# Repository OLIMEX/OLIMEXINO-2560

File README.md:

# OLIMEXINO-2560
Arduino Mega 2560 like board with ATMEGA2560 processor, 88 GPIOs, uSD card, 6-15VDC power

## License
* Software Licensee is GPL 3.0
* Hardware Licensee is CERN Open Hardware Licence v1.2
* Documentation is released under CC BY-SA 3.0

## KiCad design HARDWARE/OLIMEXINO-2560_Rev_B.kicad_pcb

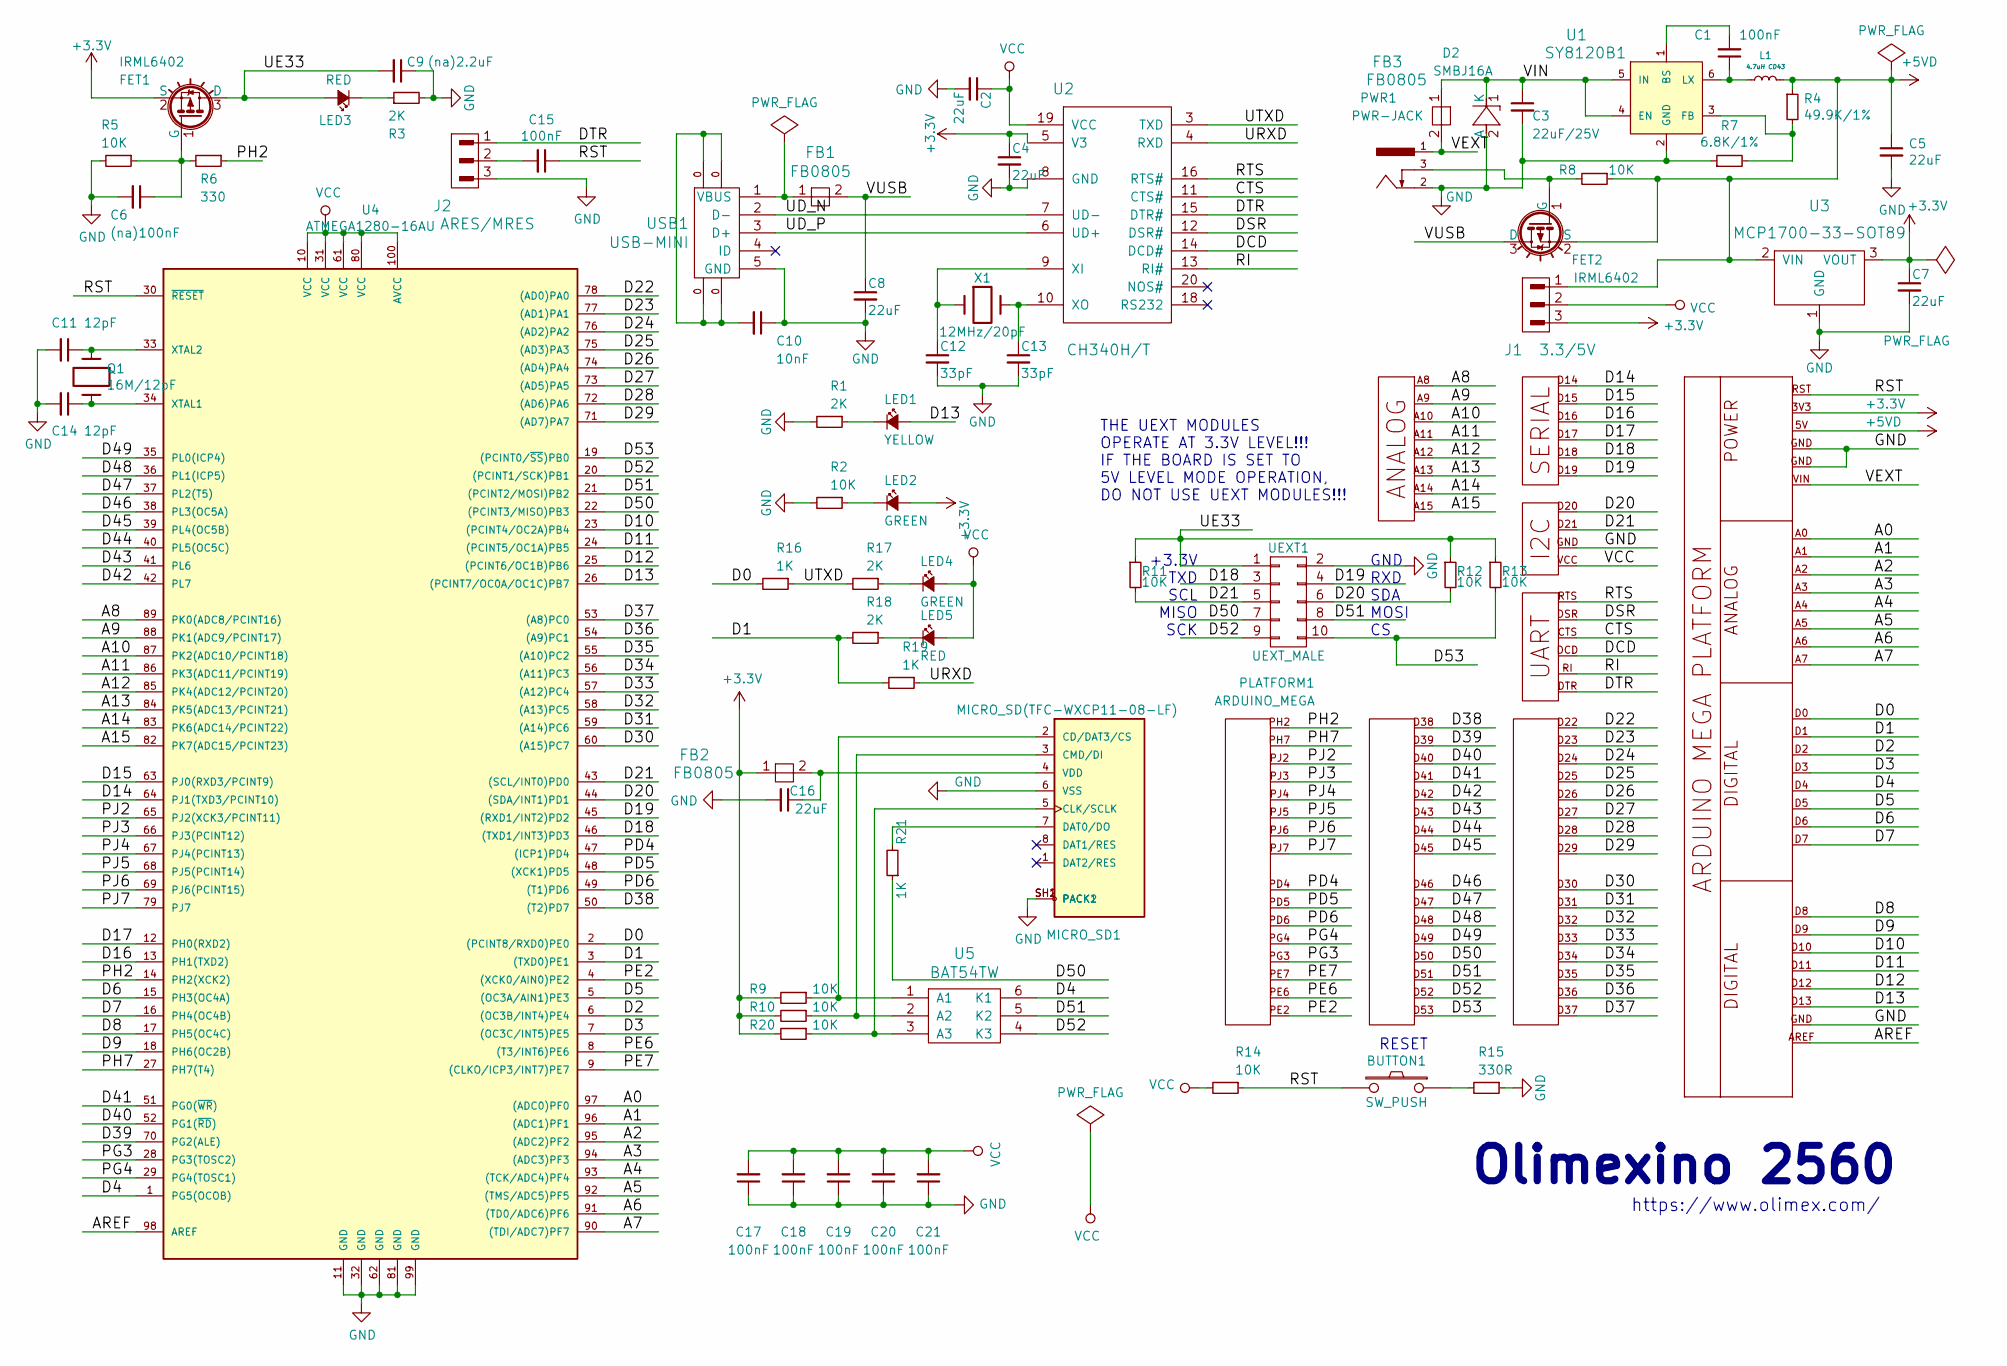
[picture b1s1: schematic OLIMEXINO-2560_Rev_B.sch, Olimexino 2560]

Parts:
BUTTON1: SW_PUSH; TSW34-W16PR-220
C1, C15, C17, C18, C19, C20, C21: 100nF; C_0402_5MIL_DWS
C2, C4, C5, C7, C8, C16: 22uF; C_0603_5MIL_DWS
C3: 22uF/25V; C_1206_5MIL_DWS
C6: (na)100nF; C_0402_5MIL_DWS
C9: (na)2.2uF; C_0603_5MIL_DWS
C10: 10nF; C_0603_5MIL_DWS
C11, C14: 12pF; C_0402_SMALL
C12, C13: 33pF; 0402
D2: SMBJ16A; SMB-KA
FB1, FB2, FB3: FB0805; L_0805_5MIL_DWS
FET1, FET2: IRML6402; SOT23
J1: 3.3/5V; HN1x3
J2: ARES/MRES; HN1x3
L1: 4.7uH CD43; CD43
LED1: YELLOW; LED_0603_KA_NOSILK
LED2, LED4: GREEN; LED_0603_KA_NOSILK
LED3, LED5: RED; LED_0603_KA_NOSILK
MICRO_SD1: MICRO_SD(TFC-WXCP11-08-LF); TFC-WXCP11-08-LF
PLATFORM1: ARDUINO_MEGA; OLIMEX_CASES-ARDUINO-MEGA-PLATFORM
PWR1: PWR-JACK; PWRJACK-FLAT
Q1: 16M/12pF; HCX-4S_2Pins_5.0x3.2mm
R1, R3, R17, R18: 2K; R_0402_5MIL_DWS
R2, R5, R8, R9, R10, R11, R12, R13, R14, R20: 10K; R_0402_5MIL_DWS
R4: 49.9K/1%; R_0603_5MIL_DWS
R6: 330; R_0402_5MIL_DWS
R7: 6.8K/1%; R_0402_5MIL_DWS
R15: 330R; R_0402_5MIL_DWS
R16, R19, R21: 1K; R_0402_5MIL_DWS
U1: SY8120B1; SOT23-6
U2: CH340H/T; SSOP-20W
U3: MCP1700-33-SOT89; SOT89
U4: ATMEGA1280-16AU; TQFP100
U5: BAT54TW; SOT363
UEXT1: UEXT_MALE; UEXT_BH10R
USB1: USB-MINI; MICRO_USB_5P-F_TYPE_DIP
X1: 12MHz/20pF; Q_49U3HMS

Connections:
+3V3: C4.1, C7.1, FB2.1, FET1.2 (S), J1.3, LED2.2 (A), PLATFORM1.3V3, R9.2, R10.2, R20.2, U2.5 (V3), U3.3 (VOUT)
+5VD: C5.1, FET2.2 (S), J1.1, L1.2, PLATFORM1.5V, R4.1, R8.1, U3.2 (VIN)
/A0: PLATFORM1.A0, U4.97 ((ADC0)PF0)
/A1: PLATFORM1.A1, U4.96 ((ADC1)PF1)
/A2: PLATFORM1.A2, U4.95 ((ADC2)PF2)
/A3: PLATFORM1.A3, U4.94 ((ADC3)PF3)
/A4: PLATFORM1.A4, U4.93 ((TCK/ADC4)PF4)
/A5: PLATFORM1.A5, U4.92 ((TMS/ADC5)PF5)
/A6: PLATFORM1.A6, U4.91 ((TD0/ADC6)PF6)
/A7: PLATFORM1.A7, U4.90 ((TDI/ADC7)PF7)
/A8: PLATFORM1.A8, U4.89 (PK0(ADC8/PCINT16))
/A9: PLATFORM1.A9, U4.88 (PK1(ADC9/PCINT17))
/A10: PLATFORM1.A10, U4.87 (PK2(ADC10/PCINT18))
/A11: PLATFORM1.A11, U4.86 (PK3(ADC11/PCINT19))
/A12: PLATFORM1.A12, U4.85 (PK4(ADC12/PCINT20))
/A13: PLATFORM1.A13, U4.84 (PK5(ADC13/PCINT21))
/A14: PLATFORM1.A14, U4.83 (PK6(ADC14/PCINT22))
/A15: PLATFORM1.A15, U4.82 (PK7(ADC15/PCINT23))
/AREF: PLATFORM1.AREF, U4.98 (AREF)
/CTS: PLATFORM1.CTS, U2.11 (CTS#)
/D0: PLATFORM1.D0, R16.2, U4.2 ((PCINT8/RXD0)PE0)
/D1: PLATFORM1.D1, R18.2, R19.2, U4.3 ((TXD0)PE1)
/D2: PLATFORM1.D2, U4.6 ((OC3B/INT4)PE4)
/D3: PLATFORM1.D3, U4.7 ((OC3C/INT5)PE5)
/D4: PLATFORM1.D4, U4.1 (PG5(OCOB)), U5.6 (K1)
/D5: PLATFORM1.D5, U4.5 ((OC3A/AIN1)PE3)
/D6: PLATFORM1.D6, U4.15 (PH3(OC4A))
/D7: PLATFORM1.D7, U4.16 (PH4(OC4B))
/D8: PLATFORM1.D8, U4.17 (PH5(OC4C))
/D9: PLATFORM1.D9, U4.18 (PH6(OC2B))
/D10: PLATFORM1.D10, U4.23 ((PCINT4/OC2A)PB4)
/D11: PLATFORM1.D11, U4.24 ((PCINT5/OC1A)PB5)
/D12: PLATFORM1.D12, U4.25 ((PCINT6/OC1B)PB6)
/D13: LED1.2 (A), PLATFORM1.D13, U4.26 ((PCINT7/OC0A/OC1C)PB7)
/D14: PLATFORM1.D14, U4.64 (PJ1(TXD3/PCINT10))
/D15: PLATFORM1.D15, U4.63 (PJ0(RXD3/PCINT9))
/D16: PLATFORM1.D16, U4.13 (PH1(TXD2))
/D17: PLATFORM1.D17, U4.12 (PH0(RXD2))
/D18: PLATFORM1.D18, U4.46 ((TXD1/INT3)PD3), UEXT1.3
/D19: PLATFORM1.D19, U4.45 ((RXD1/INT2)PD2), UEXT1.4
/D20: PLATFORM1.D20, R12.2, U4.44 ((SDA/INT1)PD1), UEXT1.6
/D21: PLATFORM1.D21, R11.2, U4.43 ((SCL/INT0)PD0), UEXT1.5
/D22: PLATFORM1.D22, U4.78 ((AD0)PA0)
/D23: PLATFORM1.D23, U4.77 ((AD1)PA1)
/D24: PLATFORM1.D24, U4.76 ((AD2)PA2)
/D25: PLATFORM1.D25, U4.75 ((AD3)PA3)
/D26: PLATFORM1.D26, U4.74 ((AD4)PA4)
/D27: PLATFORM1.D27, U4.73 ((AD5)PA5)
/D28: PLATFORM1.D28, U4.72 ((AD6)PA6)
/D29: PLATFORM1.D29, U4.71 ((AD7)PA7)
/D30: PLATFORM1.D30, U4.60 ((A15)PC7)
/D31: PLATFORM1.D31, U4.59 ((A14)PC6)
/D32: PLATFORM1.D32, U4.58 ((A13)PC5)
/D33: PLATFORM1.D33, U4.57 ((A12)PC4)
/D34: PLATFORM1.D34, U4.56 ((A11)PC3)
/D35: PLATFORM1.D35, U4.55 ((A10)PC2)
/D36: PLATFORM1.D36, U4.54 ((A9)PC1)
/D37: PLATFORM1.D37, U4.53 ((A8)PC0)
/D38: PLATFORM1.D38, U4.50 ((T2)PD7)
/D39: PLATFORM1.D39, U4.70 (PG2(ALE))
/D40: PLATFORM1.D40, U4.52 (PG1(~RD~))
/D41: PLATFORM1.D41, U4.51 (PG0(~WR~))
/D42: PLATFORM1.D42, U4.42 (PL7)
/D43: PLATFORM1.D43, U4.41 (PL6)
/D44: PLATFORM1.D44, U4.40 (PL5(OC5C))
/D45: PLATFORM1.D45, U4.39 (PL4(OC5B))
/D46: PLATFORM1.D46, U4.38 (PL3(OC5A))
/D47: PLATFORM1.D47, U4.37 (PL2(T5))
/D48: PLATFORM1.D48, U4.36 (PL1(ICP5))
/D49: PLATFORM1.D49, U4.35 (PL0(ICP4))
/D50: PLATFORM1.D50, R21.1, U4.22 ((PCINT3/MISO)PB3), UEXT1.7
/D51: PLATFORM1.D51, U4.21 ((PCINT2/MOSI)PB2), U5.5 (K2), UEXT1.8
/D52: PLATFORM1.D52, U4.20 ((PCINT1/SCK)PB1), U5.4 (K3), UEXT1.9
/D53: PLATFORM1.D53, R13.2, U4.19 ((PCINT0/~SS~)PB0), UEXT1.10
/DCD: PLATFORM1.DCD, U2.14 (DCD#)
/DSR: PLATFORM1.DSR, U2.12 (DSR#)
/DTR: J2.1, PLATFORM1.DTR, U2.15 (DTR#)
/PD4: PLATFORM1.PD4, U4.47 ((ICP1)PD4)
/PD5: PLATFORM1.PD5, U4.48 ((XCK1)PD5)
/PD6: PLATFORM1.PD6, U4.49 ((T1)PD6)
/PE2: PLATFORM1.PE2, U4.4 ((XCK0/AIN0)PE2)
/PE6: PLATFORM1.PE6, U4.8 ((T3/INT6)PE6)
/PE7: PLATFORM1.PE7, U4.9 ((CLKO/ICP3/INT7)PE7)
/PG3: PLATFORM1.PG3, U4.28 (PG3(TOSC2))
/PG4: PLATFORM1.PG4, U4.29 (PG4(TOSC1))
/PH2: PLATFORM1.PH2, R6.1, U4.14 (PH2(XCK2))
/PH7: PLATFORM1.PH7, U4.27 (PH7(T4))
/PJ2: PLATFORM1.PJ2, U4.65 (PJ2(XCK3/PCINT11))
/PJ3: PLATFORM1.PJ3, U4.66 (PJ3(PCINT12))
/PJ4: PLATFORM1.PJ4, U4.67 (PJ4(PCINT13))
/PJ5: PLATFORM1.PJ5, U4.68 (PJ5(PCINT14))
/PJ6: PLATFORM1.PJ6, U4.69 (PJ6(PCINT15))
/PJ7: PLATFORM1.PJ7, U4.79 (PJ7)
/RI: PLATFORM1.RI, U2.13 (RI#)
/RST: BUTTON1.2, C15.1, PLATFORM1.RST, R14.1, U4.30 (~RESET)
/RTS: PLATFORM1.RTS, U2.16 (RTS#)
/UD_N: U2.7 (UD-), USB1.2 (D-)
/UD_P: U2.6 (UD+), USB1.3 (D+)
/UE33: C9.2, FET1.3 (D), LED3.2 (A), R11.1, R12.1, R13.1, UEXT1.1
/URXD: R19.1, U2.4 (RXD)
/UTXD: R16.1, R17.2, U2.3 (TXD)
/VEXT: FB3.2, PLATFORM1.VIN, PWR1.1 (+)
/VIN: C3.1, D2.1 (K), FB3.1, U1.4 (EN), U1.5 (IN)
/VUSB: C8.1, FB1.2, FET2.3 (D)
GND: C2.2, C3.2, C4.2, C5.2, C6.2, C7.2, C8.2, C9.1, C10.1, C11.2, C12.2, C13.2, C14.2, C16.2, C17.1, C18.1, C19.1, C20.1, C21.1, D2.2 (A), J2.3, MICRO_SD1.6 (VSS), MICRO_SD1.SH1 (PACK1), MICRO_SD1.SH2 (PACK2), PLATFORM1.GND, PWR1.2 (-), R1.2, R2.2, R3.2, R5.2, R7.1, R15.1, U1.2 (GND), U2.8 (GND), U3.1 (GND), U4.11 (GND), U4.32 (GND), U4.62 (GND), U4.81 (GND), U4.99 (GND), UEXT1.2, USB1.5 (GND)
unnamed: BUTTON1.1, R15.2
unnamed: C1.1, L1.1, U1.6 (LX)
unnamed: C1.2, U1.1 (BS)
unnamed: C6.1, FET1.1 (G), R5.1, R6.2
unnamed: C10.2, USB1.0
unnamed: C11.1, Q1.1, U4.33 (XTAL2)
unnamed: C12.1, U2.9 (XI), X1.1
unnamed: C13.1, U2.10 (XO), X1.2
unnamed: C14.1, Q1.2, U4.34 (XTAL1)
unnamed: C15.2, J2.2
unnamed: C16.1, FB2.2, MICRO_SD1.4 (VDD)
unnamed: FB1.1, USB1.1 (VBUS)
unnamed: FET2.1 (G), PWR1.3 (-), R8.2
unnamed: LED1.1 (K), R1.1
unnamed: LED2.1 (K), R2.1
unnamed: LED3.1 (K), R3.1
unnamed: LED4.1 (K), R17.1
unnamed: LED5.1 (K), R18.1
unnamed: MICRO_SD1.2 (CD/DAT3/CS), R9.1, U5.1 (A1)
unnamed: MICRO_SD1.3 (CMD/DI), R10.1, U5.2 (A2)
unnamed: MICRO_SD1.5 (CLK/SCLK), R20.1, U5.3 (A3)
unnamed: MICRO_SD1.7 (DAT0/DO), R21.2
unnamed: R4.2, R7.2, U1.3 (FB)
VCC: C2.1, C17.2, C18.2, C19.2, C20.2, C21.2, J1.2, LED4.2 (A), LED5.2 (A), PLATFORM1.VCC, R14.2, U2.19 (VCC), U4.10 (VCC), U4.31 (VCC), U4.61 (VCC), U4.80 (VCC), U4.100 (AVCC)

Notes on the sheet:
RESET
+3.3V TXD SCL MISO SCK
GND RXD SDA MOSI CS
THE UEXT MODULES OPERATE AT 3.3V LEVEL!!! IF THE BOARD IS SET TO 5V LEVEL MODE OPERATION, DO NOT USE UEXT MODULES!!!
Olimexino 2560
https://www.olimex.com/

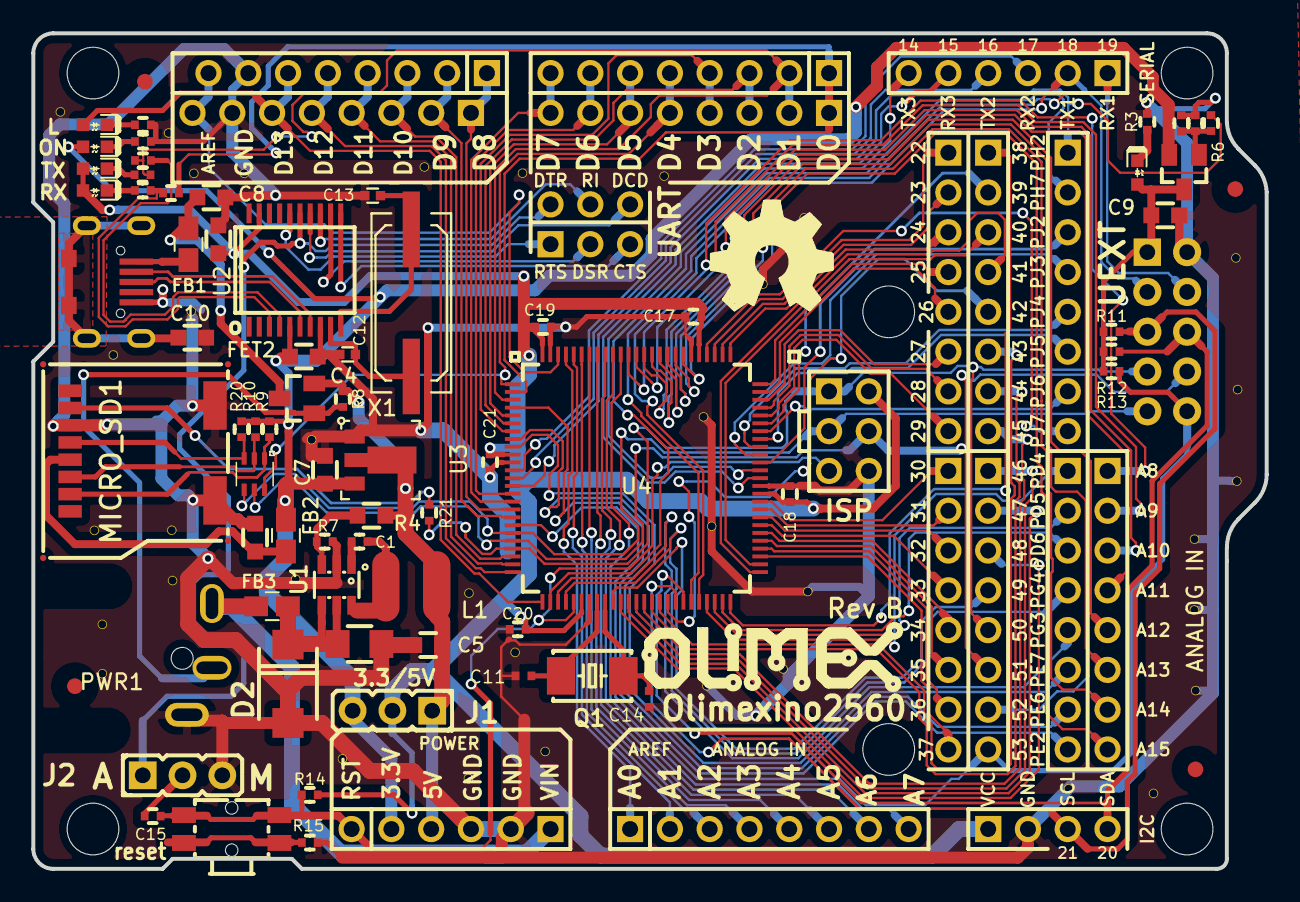
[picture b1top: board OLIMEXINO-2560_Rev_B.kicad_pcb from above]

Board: 2 copper layers, 78.7 x 53.3 mm, 73 parts (0 on the bottom side), 129 nets.

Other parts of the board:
Ref**: Val**; Fiducial1x3_transp
Ref**#2, Ref**#3, Ref**#4: Val**; Fiducial1x3_transp

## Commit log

2019-06-20 Initial upload hardware docs
2019-06-21 update users manual
